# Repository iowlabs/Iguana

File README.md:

# iow Labs Iguana

Iguana is a LoRa sensor for Smart Cities. It is an instrument designed to monitor soil temperature and humidity in real time. It is a low-cost device designed to address a wide range of scenarios. It has connectivity to different types of wireless networks (LoRa, Bt, BLE, Wifi, RF), adapting to a large number of IoT applications.

The PCB was designed with various scenarios in mind that contemplate the common needs associated with automatic irrigation, smart agriculture and soil quality monitoring. Both at the level of domestic applications and at the level of industrial applications.

The sensor considers compatibility with the following sensors:

- Soil moisture sensor ds18b20
- soil temperature sensor.
- Humidity and ambient temperature sensor.

It also has a  on board driver for a little water pump, a LoRa module, an RTC module and an SD socket for datalogger functions and an OLED screen to display instant information. Another interesting attribute is that it has an RS485 converter, which allows the iguana device to be integrated with industrial sensors for monitoring soil humidity and quality that are usually compatible with ModBus RS485 protocols.

**IoT**,**LoRa**, **Environmental measurement**, **Soil mositure**, **datalogger**, **MODBUS RS485**.

### OSHW LICENSES

## Hardware description

The PCB was designed in KiCad7 stable realease and additional components used can be found in the official [iowLabs](https://github.com/iowlabs/KiCad_Lib) library.

It has an ESP32 microcontroller, an RF95 module to integrate into LoRa and LoRaWAN network solutions. It has an RTC RV8803 and a micro SD card connector necessary to implement data logger functions.
It additionally has a "max485" module to integrate probes for quality monitoring of industrial soils based on MODBUS RS485 communication protocol.

A simple NPN-based controller allows you to integrate small water pumps to implement automatic and remote irrigation control functionalities.

An OLED display and RGB LED let you see real-time information from the sensors.

It also has a charging module for lipo batteries based on the integrated TP4056 and a charging protection circuit. Integration with solar panel based applications can be easily achieved.

To manage the power of the circuit, an MT3608 DC DC converter and a set of LDO regulators are used that power the digital electronics, the sensors and the data logger independently. The regulators that power the units can be disabled via firmware to implement low-power features.

### Dependencies
The board is based on an ESP32 microcontroller.

- USB communication through IC CH340
- Lora rfm95 module.
- microSD socket.
- RV8803 RTC module.
- max485 for RS485 communication.
- On board pump driver with a NPN 2N3904.
- On board battery charger compatible with 3.7V lipo bateries, based on TP4056.
- ws2812 RGB LED
- OLED display

### Schematic

### Layout
The layout is a 2 layers 8x5cm pcb.

| Top view | Bottom view |
| -------- | ----------- |
| ||

### BOM

The bill of materials with respective references to the LCSC part numbers of the iguana PCB components can be found in the following [link](hardware/output_files/Iguana_V1_BOM.csv).

Below is a list of the components for the probes and sensors that complement the iguana device to implement all its functionalities. The prices provided and the links are for reference only.

|  component 	| ref price 	| description 	| Link 		|
| ----------- 	| ----------- 	| ------------- | ---------	|
| Soil mositure sensor| | 	Low cost, soil moisture capacitive sensor	|			|
| Soil temperature sensor | | Sensor ds18b20 | |
| Sensor de humedad y temperatura ambiente | | SHT31 - case outdoor IP68 | |
| Sensor de Temperatura y humedad de suelo industrial | | Sensor MODBUS 485 capacitivo, de humedad y temperatura de suelo. | |
| Pantalla OLED |  | 128x64 1.3'' | |
| Batería LiPo  |  | Batería lipo 3.7V 2500mAh.Tamaño menor a 65x55cm.  | |
| Tarjeta microSD | | 16GB | |
| Batería 2012 	| | Batería 3.3V CR2012 | |

## 3D Model

The design allows the integration of the OLED and RGB LED display to monitor the status of the device and read the latest value from the sensors. it leaves exposed the connectors for the probes, the SMA connector for the LoRa antenna, and a switch to turn the device on and off.

| Cover | Base |
| -------- | ----------- |
| ||

Design view files:

- [plans](Iguna_case_V2.pdf)

The device considers a 65x54 cm 3.7V lipo battery for power. This battery can be charged externally through the USB connector or through the charging input connector.

Editable files and display plans can be found in [directorio](3Dmodel/Source_files).

The PCB design allows it to fit commercial project enclosures with IP65 standards or higher for outdoor or harsh weather applications.

## Firmware

The developed firmware represents a collection of libraries and drivers for the board's dependencies.

This collection of useful functions is implemented in the iowIguana library. However, due to the flexibility of the design, it is possible to load a wide variety of code based on other supported libraries.

The firmware was developed using PlatformIO; however, usage examples were generated for [Arduino IDE] (https://www.arduino.cc/en/software).

|  Folder  | Description |
| -----------| ----------- |
| [firmware/iguana_project](firmware/iguana_project) | The complete project compiled in its last version.|
| [firmware/examples](firmware/examples) | Arduino compatible example codes .|
| [firmware/src](firmware/src) | The source files of the library made for iguana.|

### Used libraries
Except for the uSD_iow library which is available in the official iowlabs repository, all other libraries used are available from the official Arduino and PlatformIO library manager.

- RTC 			: sparkfun/SparkFun Qwiic RTC RV8803 Arduino Library @ ^1.2.8
- Temperature sensor	: paulstoffregen/OneWire@^2.3.7
- Temperature sensor 	: milesburton/DallasTemperature@^3.11.0
- Temperature and humidity sensor : adafruit/Adafruit SHT31 Library@^2.2.2
- Temperature and humidity sensor : adafruit/Adafruit BusIO@^1.14.3
- Temperature and humidity sensor : adafruit/Adafruit Unified Sensor@^1.1.13
- ArduinoJson	:	bblanchon/ArduinoJson@^6.21.3
- OLED			: adafruit/Adafruit SH110X @ ^2.1.8
- OLED 			: adafruit/Adafruit GFX Library @ ^1.11.5
- fastLED		: fastled/FastLED@^3.6.0
- LoRa 			: sandeepmistry/LoRa @ ^0.8.0
- MQTT               : knolleary/PubSubClient@^2.8

### Available examples

| File | Description |
|---------|-------------|
| simple_version.ino  | Collect the data from the soil moisture and the soil temperature sensors, and displays it on the screen. Print the collected data in json format through the serial monitor. |
| low_energy_version.ino |  Adds a low-power mode to the simple_version code |
| lora_version.ino | Activate the LoRa module and send a message in json format. |
| mqtt_version.ino | This is an example of reading the data and sending it via MQTT to a pre-established broker.|

### Available functions

- uint8_t begin(void);
- void readSoilTemperature(void);
- void readSoilMoisture(void);
- void readSTH(void);
- void readRS485(void);
- void readSensors(void);
- String pubData(void);
- void activateSensors(uint8_t sens);
- void activateLoRa(void);
- void activateAll(void);
- void iowLogo(void);
- void showLogo(void);
- void showStatus(void);
- void showData(long time_interval);
- void saveData(void);
- void moistureCal(uint8_t val);
- void temperatureCal(uint8_t val);

## OTA UPDATE Disclaimer
- Iguana ahora es capaz de tener actualizaciones Http mediante OTA
- En la carpeta test se encuentra el archivo "OTA_update_mqtt.cpp"
- Robusto ante corte de energía durante actualización
- Existía un bug cuando se cortaba el wifi del dispositivo en medio de una actualización. Se levantaba un error de la librería WiFiClientSecurity en el archivo ssl_client.cpp
- Solución a bug: Se modifica el archivo ssl_client.cpp de forma que a penas se levante el error (linea 37) se haga ESP.restart(). Con esto OTA es robusto ante cualquier fallo testeado.
- Para que todo se encuentre en el repo, se descargaron los archivos .cpp y .h de la librería WiFiClientSecurity y se cargaron en la carpeta libs del proyecto. Esto con el fin de que el arreglo lo pueda pullear cualquiera que tome este código.

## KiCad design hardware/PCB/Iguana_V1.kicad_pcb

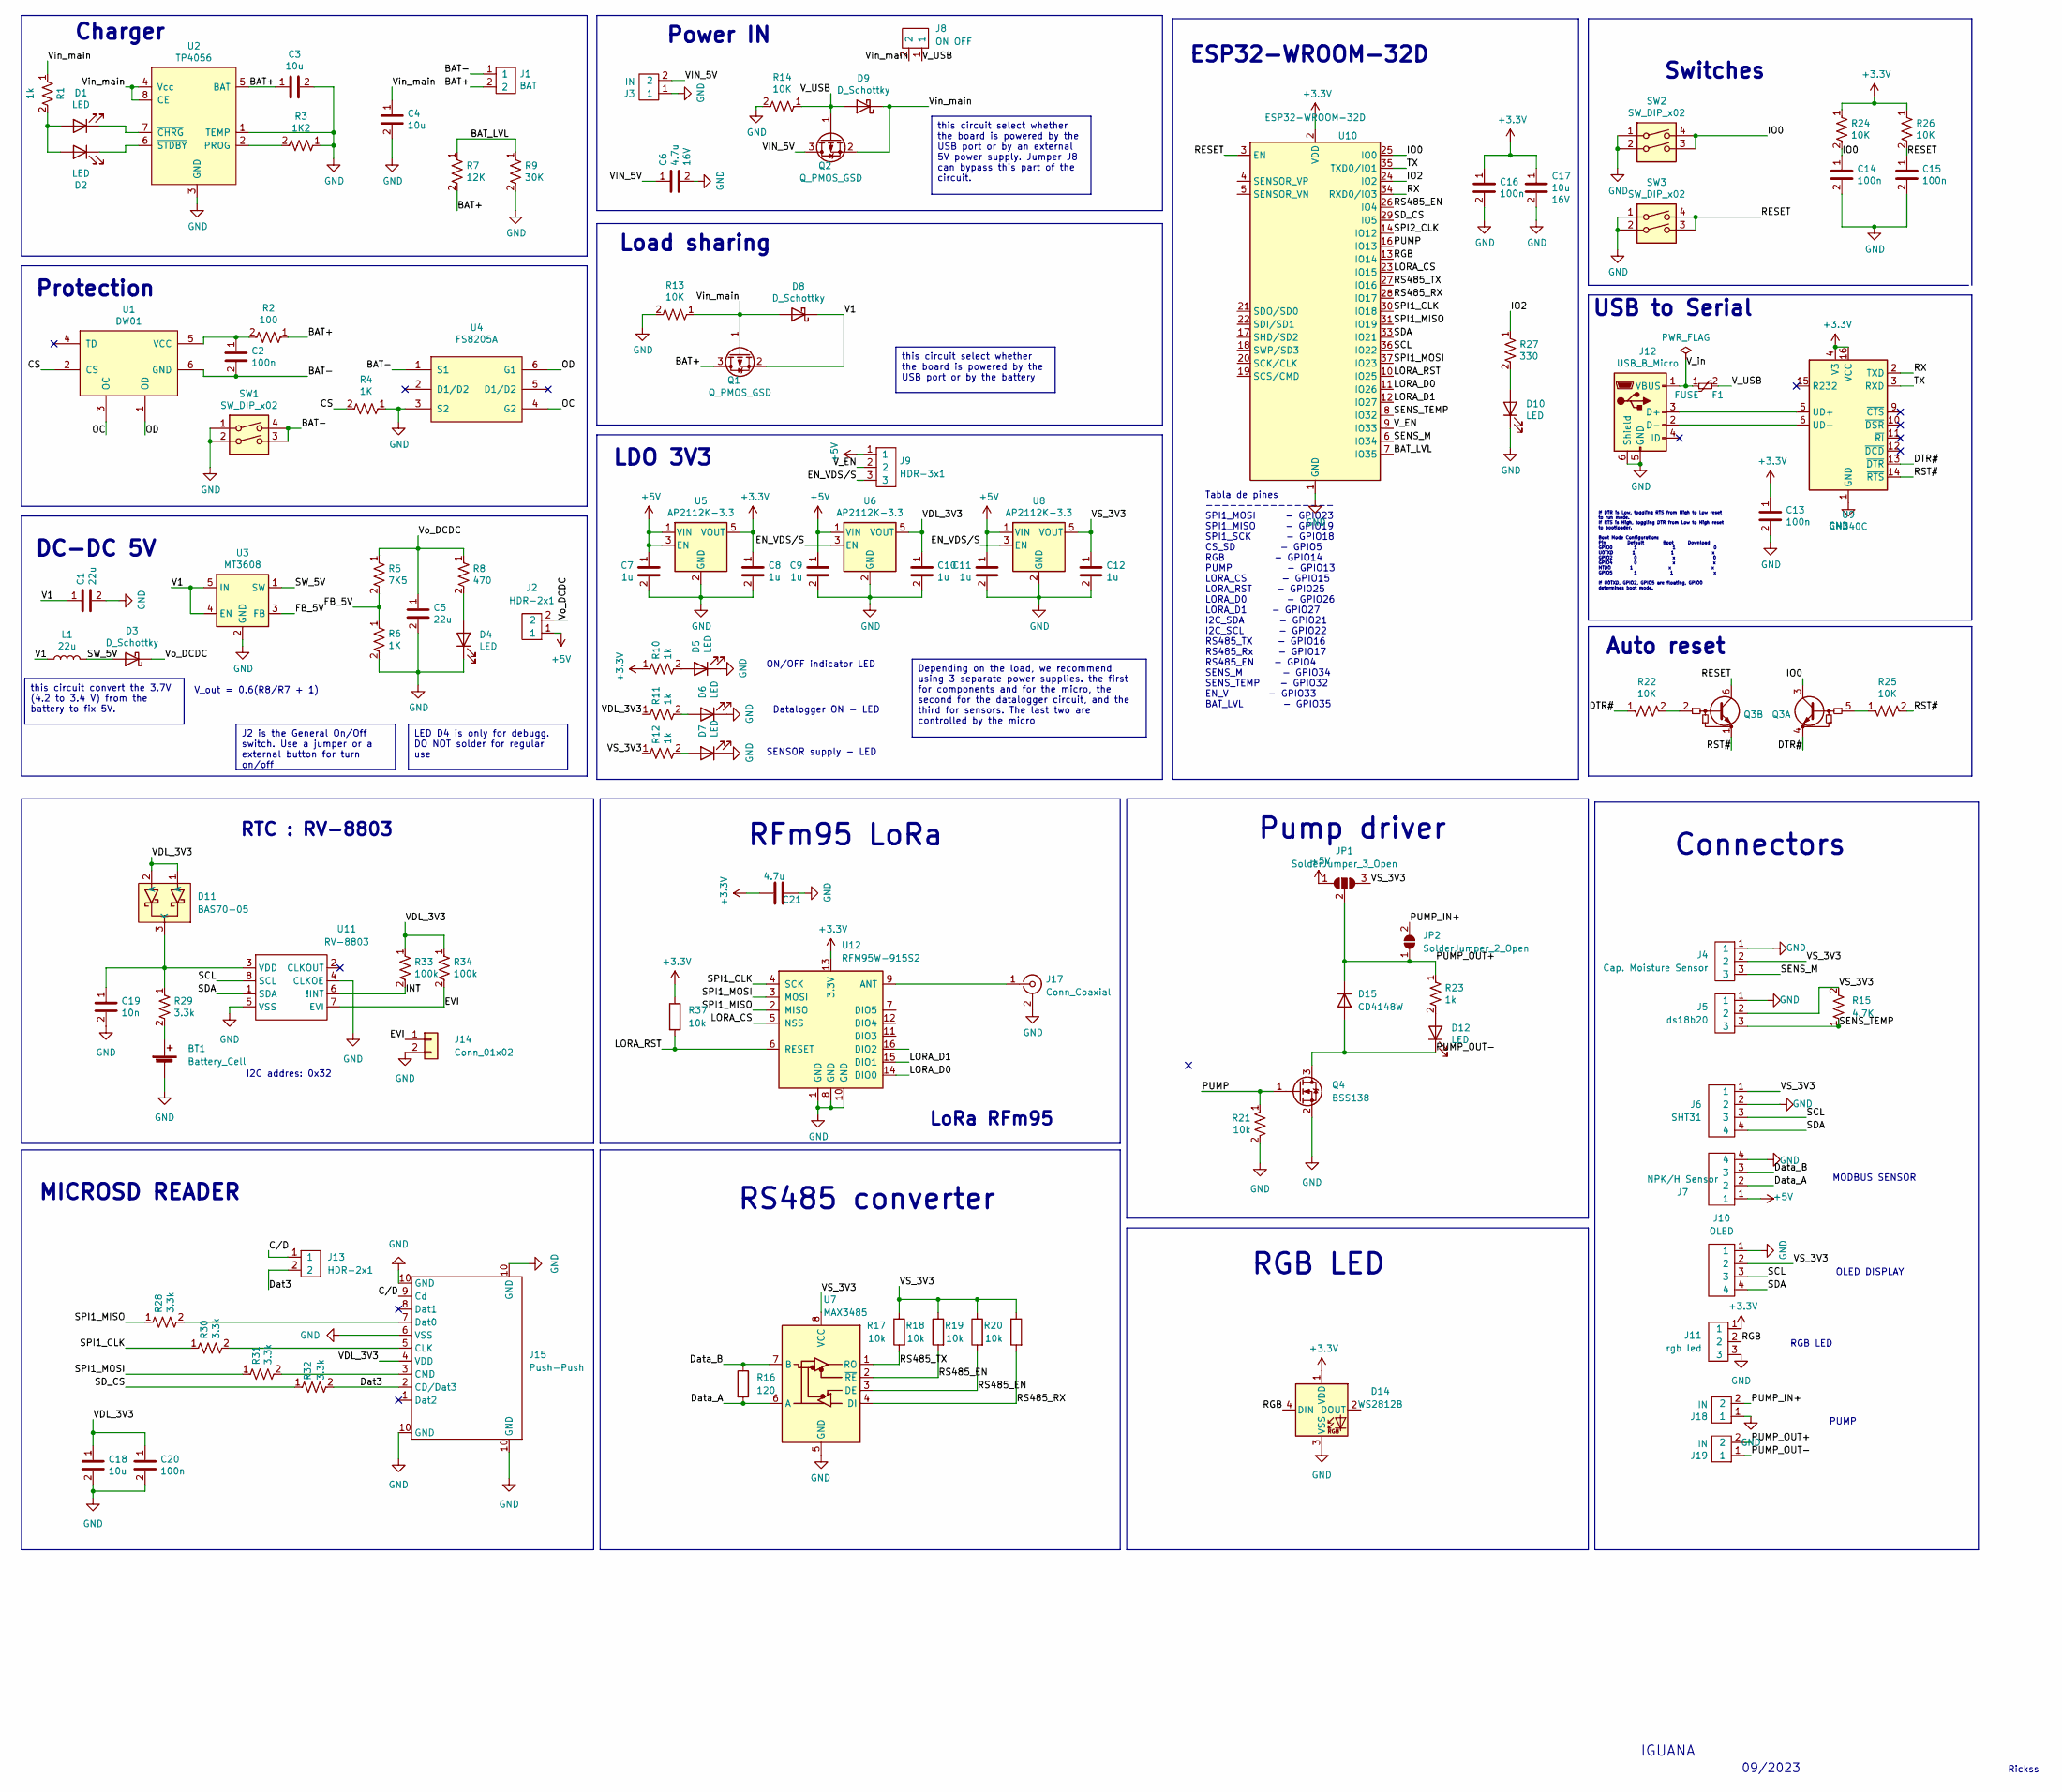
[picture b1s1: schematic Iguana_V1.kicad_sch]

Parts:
BT1: Battery_Cell; BatteryHolder_Keystone_3000_1x12mm
C1, C5: 22u; C_0805_2012Metric; Voltage rated 16V
C2, C13, C14, C15, C16, C20: 100n; C_0603_1608Metric; Voltage rated 16V
C3, C4, C17, C18: 10u; C_0805_2012Metric; Voltage rated 16V
C6: 4.7u; C_0805_2012Metric; Voltage rated 16V
C7, C8, C9, C10, C11, C12: 1u; C_0603_1608Metric; Voltage rated 16V
C19: 10n; C_0603_1608Metric; Voltage rated 16V
C21: 4.7u; C_0805_2012Metric
D1, D2, D4, D5, D6, D7, D10, D12: LED; LED_0603_1608Metric
D3, D8, D9: D_Schottky; D_SMA
D11: BAS70-05; SOT-23
D14: WS2812B; LED_WS2812B_PLCC4_5.0x5.0mm_P3.2mm
D15: CD4148W; D_0805_2012Metric
F1: FUSE; Fuse_1206_3216Metric
J1: BAT; JST_XH_B2B-XH-A_1x02_P2.50mm_Vertical
J2: HDR-2x1; PinHeader_1x02_P2.54mm_Vertical
J3, J18, J19: IN; JST_XH_B2B-XH-A_1x02_P2.50mm_Vertical
J4: Cap. Moisture Sensor; JST_XH_B3B-XH-A_1x03_P2.50mm_Vertical
J5: ds18b20; JST_XH_B3B-XH-A_1x03_P2.50mm_Vertical
J6: SHT31; JST_XH_B4B-XH-A_1x04_P2.50mm_Vertical
J7: NPK/H Sensor; JST_XH_B4B-XH-A_1x04_P2.50mm_Vertical
J8: ON OFF; SolderJumper-2_P1.3mm_Open_RoundedPad1.0x1.5mm
J9: HDR-3x1; SolderJumper-3_P1.3mm_Open_RoundedPad1.0x1.5mm_NumberLabels
J10: OLED; JST_XH_B4B-XH-A_1x04_P2.50mm_Vertical
J11: rgb led; JST_XH_B3B-XH-A_1x03_P2.50mm_Vertical
J12: USB_B_Micro; USB_Micro-B_Amphenol_10118194_Horizontal
J13: HDR-2x1; SolderJumper-2_P1.3mm_Open_RoundedPad1.0x1.5mm
J14: Conn_01x02; SolderJumper-2_P1.3mm_Open_RoundedPad1.0x1.5mm
J15: microSD_push_push
J17: Conn_Coaxial; U.FL_Molex_MCRF_73412-0110_Vertical
JP1: SolderJumper_3_Open; SolderJumper-3_P1.3mm_Open_RoundedPad1.0x1.5mm
JP2: SolderJumper_2_Open; SolderJumper-2_P1.3mm_Open_RoundedPad1.0x1.5mm
L1: 22u; L_Bourns_SRP7028A_7.3x6.6mm
Q1, Q2: Q_PMOS_GSD; SOT-23
Q3: Q_Dual_NPN_NPN_BRT_E1B1C2E2B2C1; SOT-363_SC-70-6_Handsoldering
Q4: BSS138; SOT-23
R1, R10, R11, R12, R23: 1k; R_0603_1608Metric
R2: 100; R_0603_1608Metric
R3: 1K2; R_0603_1608Metric
R4, R6: 1K; R_0603_1608Metric
R5: 7K5; R_0603_1608Metric
R7: 12K; R_0603_1608Metric
R8: 470; R_0603_1608Metric
R9: 30K; R_0603_1608Metric
R13, R14, R22, R24, R25, R26: 10K; R_0603_1608Metric
R15: 4.7K; R_0603_1608Metric
R16: 120; R_0603_1608Metric
R17, R18, R19, R20, R21, R37: 10k; R_0603_1608Metric
R27: 330; R_0603_1608Metric
R28, R29, R30, R31, R32: 3.3k; R_0603_1608Metric
R33, R34: 100k; R_0603_1608Metric
SW1, SW2, SW3: SW_DIP_x02; SMD_SWITCH
U1: DW01; SOT-23-6
U2: TP4056; TP4056_SOP-8-PP
U3: MT3608; SOT-23-6
U4: FS8205A; SOT-23-6
U5, U6, U8: AP2112K-3.3; SOT-23-5
U7: MAX3485; SOP-8_3.9x4.9mm_P1.27mm
U9: CH340C; SOIC-16_3.9x9.9mm_P1.27mm
U10: ESP32-WROOM-32D; ESP32-WROOM-32
U11: RV-8803; SON-8
U12: RFM95W-915S2; HOPERF_RFM69HW

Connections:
+3V3: C8.1, C13.1, C16.1, C17.1, C21.2, D14.1 (VDD), J11.1, R10.1, R24.1, R26.1, R37.1, U5.5 (VOUT), U9.4 (V3), U9.16 (VCC), U10.2 (VDD), U12.13 (3.3V)
+5V: C7.1, C9.1, C11.1, J2.1, J7.1, J9.1, JP1.1 (A), U5.1 (VIN), U5.3 (EN), U6.1 (VIN), U8.1 (VIN)
/BAT+: C3.1, J1.2, Q1.3 (D), R2.1, R7.2, U2.5 (BAT)
/BAT-: C2.2, J1.1, SW1.3, SW1.4, U1.6 (GND), U4.1 (S1)
/BAT_LVL: R7.1, R9.1, U10.7 (IO35)
/CS: R4.2, U1.2 (CS)
/C/D: J13.1, J15.9 (Cd)
/DTR#: Q3.4 (E1), R22.1, U9.13 (~DTR)
/Dat3: J13.2, J15.2 (CD/Dat3), R32.2
/Data_A: J7.2, R16.2, U7.6 (A)
/Data_B: J7.3, R16.1, U7.7 (B)
/EN_VDS/S: J9.3, U6.3 (EN), U8.3 (EN)
/EVI: J14.1, R34.2, U11.7 (EVI)
/FB_5V: R5.2, R6.1, U3.3 (FB)
/INT: R33.2, U11.6 (!INT)
/IO0: C14.1, Q3.3 (C1), R24.2, SW2.3, SW2.4, U10.25 (IO0)
/IO2: R27.1, U10.24 (IO2)
/LORA_CS: U10.23 (IO15), U12.5 (NSS)
/LORA_D0: U10.11 (IO26), U12.14 (DIO0)
/LORA_D1: U10.12 (IO27), U12.15 (DIO1)
/LORA_RST: R37.2, U10.10 (IO25), U12.6 (RESET)
/OC: U1.3 (OC), U4.4 (G2)
/OD: U1.1 (OD), U4.6 (G1)
/PUMP: Q4.1 (G), R21.1, U10.16 (IO13)
/PUMP_IN+: J18.2, JP2.2 (B)
/PUMP_OUT+: D15.1 (K), J19.2, JP1.2 (C), JP2.1 (A), R23.1
/PUMP_OUT-: D12.1 (K), D15.2 (A), J19.1, Q4.3 (D)
/RESET: C15.1, Q3.6 (C1), R26.2, SW3.3, SW3.4, U10.3 (EN)
/RGB: D14.4 (DIN), J11.2, U10.13 (IO14)
/RS485_EN: R18.2, R19.2, U7.2 (~RE), U7.3 (DE), U10.26 (IO4)
/RS485_RX: R20.2, U7.4 (DI), U10.28 (IO17)
/RS485_TX: R17.2, U7.1 (RO), U10.27 (IO16)
/RST#: Q3.1 (E1), R25.2, U9.14 (~RTS)
/RX: U9.2 (TXD), U10.34 (RXD0/IO3)
/SCL: J6.3, J10.3, U10.36 (IO22), U11.8 (SCL)
/SDA: J6.4, J10.4, U10.33 (IO21), U11.1 (SDA)
/SD_CS: R32.1, U10.29 (IO5)
/SENS_M: J4.3, U10.6 (IO34)
/SENS_TEMP: J5.3, R15.1, U10.8 (IO32)
/SPI1_CLK: R30.1, U10.30 (IO18), U12.4 (SCK)
/SPI1_MISO: R28.1, U10.31 (IO19), U12.2 (MISO)
/SPI1_MOSI: R31.1, U10.37 (IO23), U12.3 (MOSI)
/SPI2_CLK: U10.14 (IO12)
/SW_5V: D3.2 (A), L1.2, U3.1 (SW)
/TX: U9.3 (RXD), U10.35 (TXD0/IO1)
/V1: C1.1, D8.1 (K), L1.1, Q1.2 (S), U3.4 (EN), U3.5 (IN)
/VDL_3V3: C10.1, C18.1, C20.1, D11.1 (A), D11.2 (A), J15.4 (VDD), R11.1, R33.1, R34.1, U6.5 (VOUT)
/VIN_5V: C6.1, J3.2, Q2.3 (D)
/VS_3V3: C12.1, J4.2, J5.2, J6.1, J10.2, JP1.3 (B), R12.1, R15.2, R17.1, R18.1, R19.1, R20.1, U7.8 (VCC), U8.5 (VOUT)
/V_EN: J9.2, U10.9 (IO33)
/V_USB: D9.2 (A), F1.2, J8.1, Q2.1 (G), R14.1
/V_in: F1.1, J12.1 (VBUS)
/Vin_main: C4.1, D8.2 (A), D9.1 (K), J8.2, Q1.1 (G), Q2.2 (S), R1.1, R13.1, U2.4 (Vcc), U2.8 (CE)
/Vo_DCDC: C5.1, D3.1 (K), J2.2, R5.1, R8.1
GND: BT1.2 (-), C1.2, C3.2, C4.2, C5.2, C6.2, C7.2, C8.2, C9.2, C10.2, C11.2, C12.2, C13.2, C14.2, C15.2, C16.2, C17.2, C18.2, C19.2, C20.2, C21.1, D4.1 (K), D5.1 (K), D6.1 (K), D7.1 (K), D10.1 (K), D14.3 (VSS), J3.1, J4.1, J5.1, J6.2, J7.4, J10.1, J11.3, J12.5 (GND), J12.6 (Shield), J14.2, J15.6 (VSS), J15.10 (GND), J17.2 (Ext), J18.1, Q4.2 (S), R3.1, R4.1, R6.2, R9.2, R13.2, R14.2, R21.2, SW1.1, SW1.2, SW2.1, SW2.2, SW3.1, SW3.2, U2.1 (TEMP), U2.3 (GND), U3.2 (GND), U4.3 (S2), U5.2 (GND), U6.2 (GND), U7.5 (GND), U8.2 (GND), U9.1 (GND), U10.1 (GND), U10.15 (GND), U10.38 (GND), U10.39 (GND), U11.4 (CLKOE), U11.5 (VSS), U12.1 (GND), U12.8 (GND), U12.10 (GND)
unnamed: BT1.1 (+), R29.2
unnamed: D1.2 (A), D2.2 (A), R1.2
unnamed: D1.1 (K), U2.7 (~CHRG)
unnamed: D2.1 (K), U2.6 (~STDBY)
unnamed: D4.2 (A), R8.2
unnamed: D5.2 (A), R10.2
unnamed: D6.2 (A), R11.2
unnamed: D7.2 (A), R12.2
unnamed: D10.2 (A), R27.2
unnamed: C19.1, D11.3 (K), R29.1, U11.3 (VDD)
unnamed: D12.2 (A), R23.2
unnamed: J12.3 (D+), U9.5 (UD+)
unnamed: J12.2 (D-), U9.6 (UD-)
unnamed: J15.5 (CLK), R30.2
unnamed: J15.3 (CMD), R31.2
unnamed: J15.7 (Dat0), R28.2
unnamed: J17.1 (In), U12.9 (ANT)
unnamed: Q3.5 (B1), R25.1
unnamed: Q3.2 (B1), R22.2
unnamed: C2.1, R2.2, U1.5 (VCC)
unnamed: R3.2, U2.2 (PROG)

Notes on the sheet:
this circuit select whether the board is powered by the USB port or by the battery
this circuit select whether the board is powered by the USB port or by an external 5V power supply. Jumper J8 can bypass this part of the circuit.
LED D4 is only for debugg. DO NOT solder for regular use
this circuit convert the 3.7V (4.2 to 3.4 V) from the battery to fix 5V.
J2 is the General On/Off switch. Use a jumper or a external button for turn on/off
Depending on the load, we recommend using 3 separate power supplies. the first for components and for the micro, the second for the datalogger circuit, and the third for sensors. The last two are controlled by the micro
I2C addres: 0x32
DC-DC 5V
Tabla de pines ---------------- SPI1_MOSI - GPIO23 SPI1_MISO - GPIO19 SPI1_SCK - GPIO18 CS_SD - GPIO5 RGB - GPIO14 PUMP - GPIO13 LORA_CS - GPIO15 LORA_RST - GPIO25 LORA_D0 - GPIO26 LORA_D1 - GPIO27 I2C_SDA - GPIO21 I2C_SCL - GPIO22 RS485_TX - GPIO16 RS485_Rx - GPIO17 RS485_EN - GPIO4 SENS_M - GPIO3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
ON/OFF indicator LED
Power IN
RTC : RV-8803
Auto reset
USB to Serial
Connectors
PUMP
IGUANA
MICROSD READER
09/2023
If DTR is Low, toggling RTS from High to Low reset to run mode. If RTS is High, toggling DTR from Low to High reset to bootloader. Boot Mode Configuration: Pin Default Boot Download GPIO0 1 1 0 U0TXD 1 1 x GPIO2 0 x 0 GPIO4 0 x x MTDO 1 x x GPIO5 1 1 x If U0TXD, GPIO2, GPIO5 are floating, GPIO0 det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
RS485 converter
Load sharing
ESP32-WROOM-32D
RFm95 LoRa
Pump driver
Charger
Switches
LoRa RFm95
RGB LED
Rickss
V_out = 0.6(R8/R7 + 1)
SENSOR supply - LED
Protection
Datalogger ON - LED
OLED DISPLAY
MODBUS SENSOR
LDO 3V3

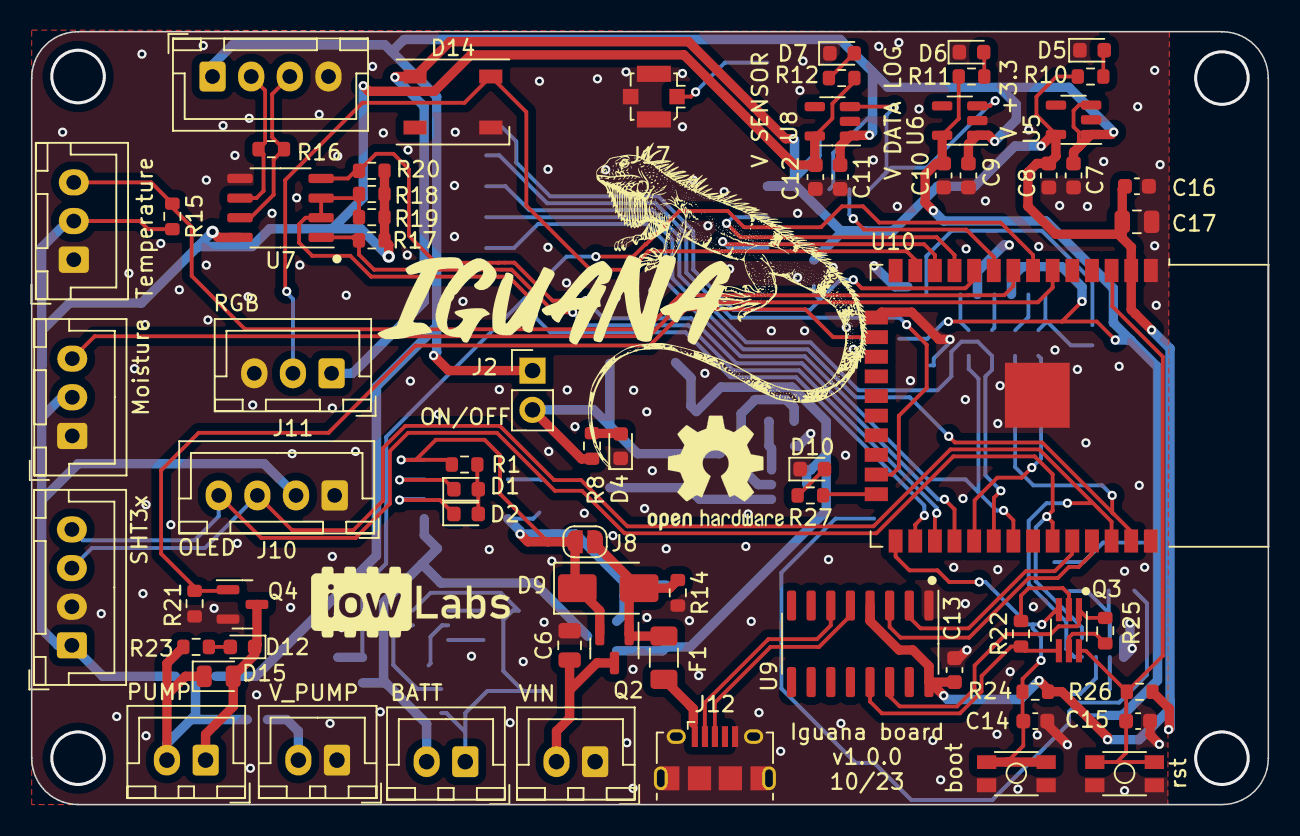
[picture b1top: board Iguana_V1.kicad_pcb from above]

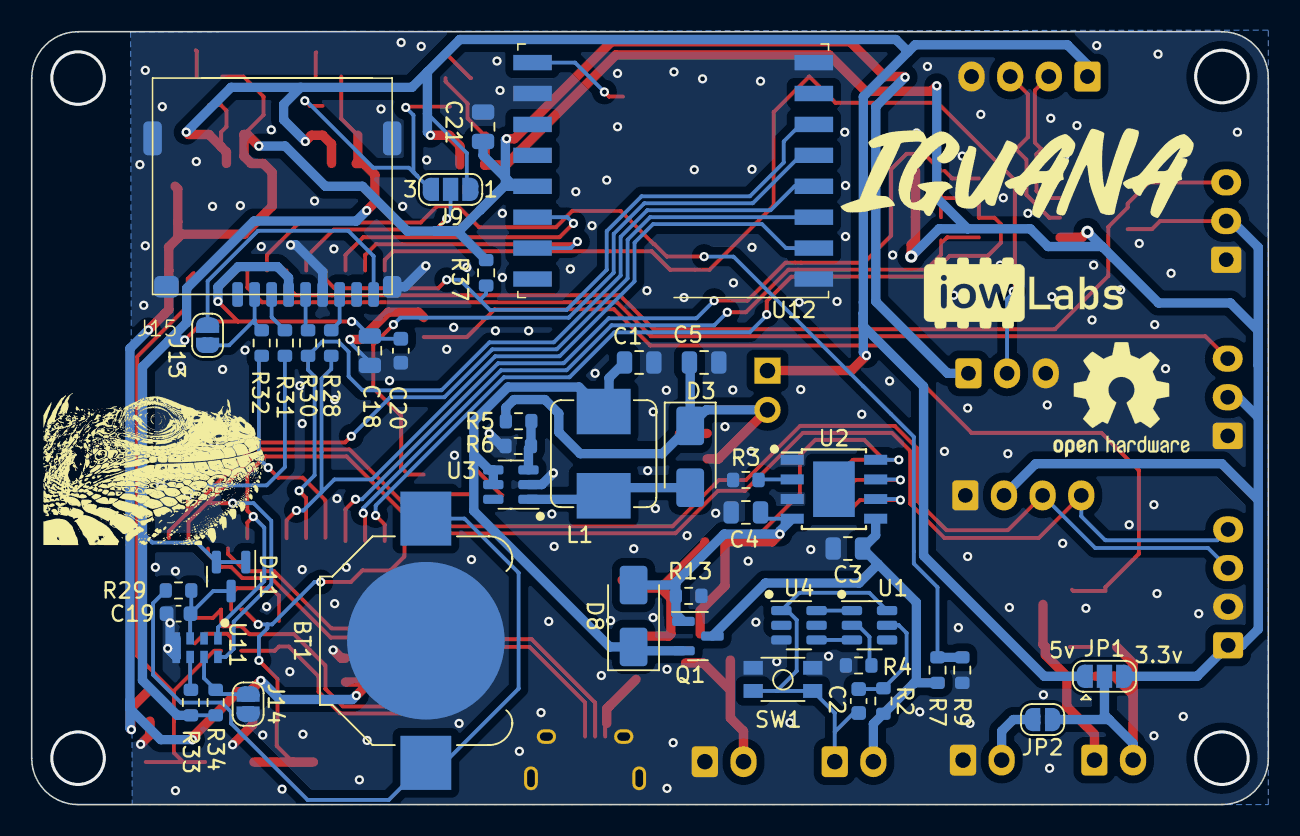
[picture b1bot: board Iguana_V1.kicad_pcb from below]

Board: 2 copper layers, 80.0 x 50.0 mm, 112 parts (44 on the bottom side), 75 nets.

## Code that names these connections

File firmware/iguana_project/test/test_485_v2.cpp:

#include <Arduino.h>

#define SERIAL_RS485 Serial2
#define RS485_BR 	 4800

#define LED          2 // on board led
#define I2C_SCL      22
#define I2C_SDA      21

#define SD_CS        5 //VSPI
#define SD_MISO      19
#define SD_MOSI      23
#define SD_CLK       18

#define RFM_CS       15 //HPSI
#define RFM_RST      25
#define RFM_DIO0     26
#define RFM_DIO1     27

#define RS485_TX     16 //HARDWARE SERIAL 2
#define RS485_RX     17 //HARDWARE SERIAL 2
#define RS485_EN     4
#define V_EN		 33

#define PUMP       	13
#define RGB        	14
#define SENS_TEMP  	32
#define SENS_M    	34
#define BAT_LVL    	35

//NTU/SST
//byte rs485_trama[8] = {0x01,0x03,0x00,0x00,0x00,0x02,0xC4,0xB0};//
//byte rs485_trama[8] = {0x01,0x03,0x00,0x01,0x00,0x01,0xD5,0xCA};//
byte rs485_trama[8] = {0x01,0x03,0x00,0x00,0x00,0x01,0x84,0x0A};//
byte rs485_rcv_buff [15];
byte rs485_temp_buff[4] , rs485_header_buff[3], rs485_val_buff[2];
int moisture_int 	= 0;
float moisture 	= 0.0;

void setup()
{
	Serial.begin(115200);
  	SERIAL_RS485.begin(RS485_BR, RS485_TX, RS485_RX);
	pinMode(LED,OUTPUT);
  	pinMode(V_EN,OUTPUT);
	pinMode(RS485_EN,OUTPUT);

	digitalWrite(V_EN  ,HIGH);
	digitalWrite(RS485_EN  ,LOW);

	Serial.println("Setup Ready");
}

void loop()
{
	//TRY WITH 410 TRAMA
    digitalWrite(RS485_EN,HIGH);
    SERIAL_RS485.write(rs485_trama,8);
    SERIAL_RS485.flush();
    digitalWrite(RS485_EN,LOW);
    delay(100);


  	  SERIAL_RS485.readBytes(rs485_rcv_buff,7);
  	  for (int i = 0; i<8;i++)
  	  {
  		  Serial.print(rs485_rcv_buff[i], HEX); // Print the received byte in HEX format
  		  Serial.print(",");


  	  }
    Serial.println();

    for(int i = 0; i<3 ; i++){ rs485_header_buff[i] = rs485_rcv_buff[i];}
    for(int i = 0; i<2 ; i++){ rs485_val_buff[i] 	= rs485_rcv_buff[i];}

    //CONVERT DATA TO FLOAT
    moisture_int = int(rs485_val_buff[0]<<8 | rs485_val_buff[1]);
    Serial.println(moisture_int);
    Serial.println(moisture_int/100.0);
    delay(30000);

}

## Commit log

2023-08-29 Firmware Creation
    Firmare to read humidity and temperature for soils and ambient.
2023-08-30 Updated Firmware
    Implemented Deep Sleep and Json
2023-09-11 PCB Updated
2023-09-22 testing working on readme
2023-09-23 adding relay and working on pcb
2023-09-29 replace relay. working on pcb
2023-09-29 pcb almost ready
2023-10-03 pcb finished
2023-10-14 Added circles on edgecut.
    Added circles where the drill holes were suppossed to go for the .step file be created with holes.
2023-10-16 pcb minor changes
2023-10-26 starting firmware
2023-10-26 3D Files Uploaded
    V1 Iguana Case Files Uploaded
2023-11-02 Firmware Update
    Test done, Oled don't work, fix that
2023-11-06 organizing the schematic. firmware lib v1 working.
2023-11-10 deleted test oled
2023-11-12 Changed something
2023-11-13 3D Files Uploaded
2023-11-14 workng on readme
2023-11-14 Planos Finales Iguana
2023-11-15 Update iowIguana.cpp
    Display Improvements
2023-11-15 adding structure images
2023-11-15 Display Updated
    AutoConnect Test Created on /test
2023-11-20 no c
2023-12-13 Stuff
2024-01-03 testing modbus code
2024-01-03 arreglo de medicion sensor RS485
2024-01-04 se agrega repo con .bin para OTA UPDATE
2024-01-04 actualizacion de firmware. Se incluye OTA update con link de github
2024-01-04 se agregan librerias para solucionar bug de OTA cuando se cae la wifi en mitad del update
2024-01-04 Update README.md
    OTA UPDATE
2024-01-05 ota_try
2024-01-10 Implementacion de Deep Sleep y MQTT en Iguana
2024-01-16 testing simple lora mode
2024-01-16 Recepcion y envio MQTT y rutina Deep Sleep
2024-01-16 Update README.md
    Typo
2024-01-23 mqtt comands
2024-01-23 integracion de deepsleep y mqtt con comandos. Falta integrar bien OTA con aws por los certificados y mejorar el sistema de comandos para incluir funcionalidades de cambiar el tiempo de deep sleep u o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
2024-01-29 Codigos Deep Sleep comentados
2024-01-31 3D Model Update
    Structural issues noticed when assembly, fixed them on the 3D Model
